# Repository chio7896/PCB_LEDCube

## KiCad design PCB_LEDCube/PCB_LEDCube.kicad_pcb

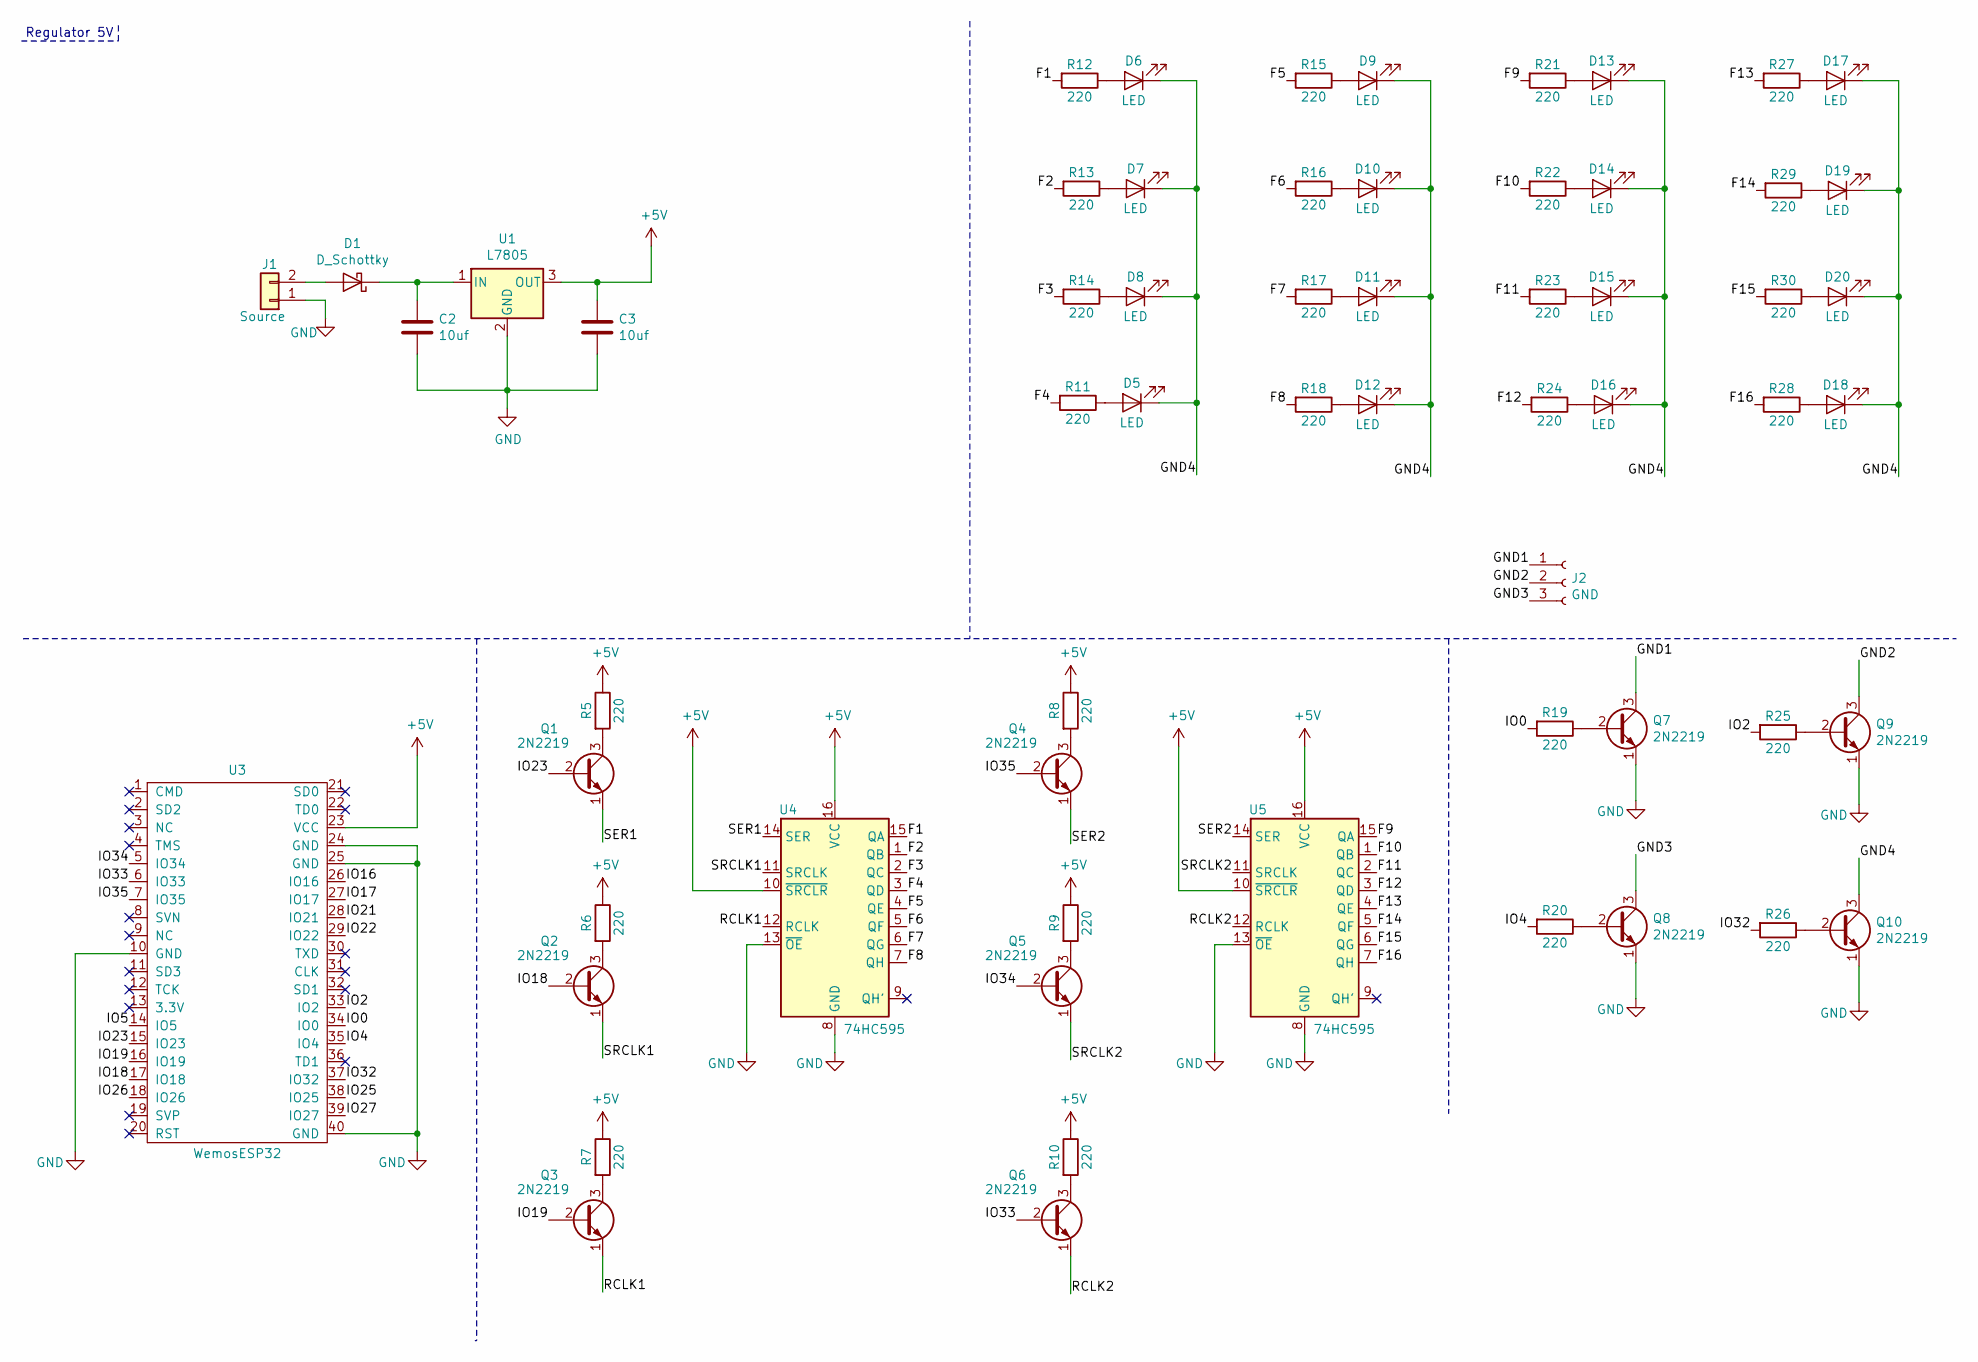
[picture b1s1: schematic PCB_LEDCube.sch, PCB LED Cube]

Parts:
C2, C3: 10uf; C_Disc_D5.0mm_W2.5mm_P5.00mm
D1: D_Schottky; D_A-405_P7.62mm_Horizontal
D5, D6, D7, D8, D9, D10, D11, D12, D13, D14, D15, D16, D17, D18, D19, D20: LED; LED_D5.0mm
J1: Source; TerminalBlock_bornier-2_P5.08mm
J2: GND; PinHeader_1x03_P2.54mm_Vertical
Q1, Q2, Q3, Q4, Q5, Q6, Q7, Q8, Q9, Q10: 2N2219; TO-92L_Inline
R5, R6, R7, R8, R9, R10, R11, R12, R13, R14, R15, R16, R17, R18, R19, R20, R21, R22, R23, R24, R25, R26, R27, R28, R29, R30: 220; R_Axial_DIN0207_L6.3mm_D2.5mm_P7.62mm_Horizontal
U1: L7805; TO-220-3_Vertical
U3: WemosESP32; Wemos_ESP32
U4, U5: 74HC595; DIP-16_W10.16mm_LongPads

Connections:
+5V: C3.1, R5.1, R6.1, R7.1, R8.1, R9.1, R10.1, U1.3 (OUT), U3.23 (VCC), U4.10 (~SRCLR), U4.16 (VCC), U5.10 (~SRCLR), U5.16 (VCC)
/F1: R12.2, U4.15 (QA)
/F2: R13.2, U4.1 (QB)
/F3: R14.2, U4.2 (QC)
/F4: R11.2, U4.3 (QD)
/F5: R15.2, U4.4 (QE)
/F6: R16.2, U4.5 (QF)
/F7: R17.2, U4.6 (QG)
/F8: R18.2, U4.7 (QH)
/F9: R21.2, U5.15 (QA)
/F10: R22.2, U5.1 (QB)
/F11: R23.2, U5.2 (QC)
/F12: R24.2, U5.3 (QD)
/F13: R27.2, U5.4 (QE)
/F14: R29.2, U5.5 (QF)
/F15: R30.2, U5.6 (QG)
/F16: R28.2, U5.7 (QH)
/GND1: J2.1, Q7.3 (C)
/GND2: J2.2, Q9.3 (C)
/GND3: J2.3, Q8.3 (C)
/GND4: D5.1 (K), D6.1 (K), D7.1 (K), D8.1 (K), D9.1 (K), D10.1 (K), D11.1 (K), D12.1 (K), D13.1 (K), D14.1 (K), D15.1 (K), D16.1 (K), D17.1 (K), D18.1 (K), D19.1 (K), D20.1 (K), Q10.3 (C)
/IO0: R19.2, U3.34 (IO0)
/IO2: R25.2, U3.33 (IO2)
/IO4: R20.2, U3.35 (IO4)
/IO5: U3.14 (IO5)
/IO16: U3.26 (IO16)
/IO17: U3.27 (IO17)
/IO18: Q2.2 (B), U3.17 (IO18)
/IO19: Q3.2 (B), U3.16 (IO19)
/IO21: U3.28 (IO21)
/IO22: U3.29 (IO22)
/IO23: Q1.2 (B), U3.15 (IO23)
/IO25: U3.38 (IO25)
/IO26: U3.18 (IO26)
/IO27: U3.39 (IO27)
/IO32: R26.2, U3.37 (IO32)
/IO33: Q6.2 (B), U3.6 (IO33)
/IO34: Q5.2 (B), U3.5 (IO34)
/IO35: Q4.2 (B), U3.7 (IO35)
/RCLK1: Q3.1 (E), U4.12 (RCLK)
/RCLK2: Q6.1 (E), U5.12 (RCLK)
/SER1: Q1.1 (E), U4.14 (SER)
/SER2: Q4.1 (E), U5.14 (SER)
/SRCLK1: Q2.1 (E), U4.11 (SRCLK)
/SRCLK2: Q5.1 (E), U5.11 (SRCLK)
GND: C2.2, C3.2, J1.1, Q7.1 (E), Q8.1 (E), Q9.1 (E), Q10.1 (E), U1.2 (GND), U3.10 (GND), U3.24 (GND), U3.25 (GND), U3.40 (GND), U4.8 (GND), U4.13 (~OE), U5.8 (GND), U5.13 (~OE)
unnamed: C2.1, D1.1 (K), U1.1 (IN)
unnamed: D1.2 (A), J1.2
unnamed: D5.2 (A), R11.1
unnamed: D6.2 (A), R12.1
unnamed: D7.2 (A), R13.1
unnamed: D8.2 (A), R14.1
unnamed: D9.2 (A), R15.1
unnamed: D10.2 (A), R16.1
unnamed: D11.2 (A), R17.1
unnamed: D12.2 (A), R18.1
unnamed: D13.2 (A), R21.1
unnamed: D14.2 (A), R22.1
unnamed: D15.2 (A), R23.1
unnamed: D16.2 (A), R24.1
unnamed: D17.2 (A), R27.1
unnamed: D18.2 (A), R28.1
unnamed: D19.2 (A), R29.1
unnamed: D20.2 (A), R30.1
unnamed: Q1.3 (C), R5.2
unnamed: Q2.3 (C), R6.2
unnamed: Q3.3 (C), R7.2
unnamed: Q4.3 (C), R8.2
unnamed: Q5.3 (C), R9.2
unnamed: Q6.3 (C), R10.2
unnamed: Q7.2 (B), R19.1
unnamed: Q8.2 (B), R20.1
unnamed: Q9.2 (B), R25.1
unnamed: Q10.2 (B), R26.1

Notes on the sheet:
Regulator 5V

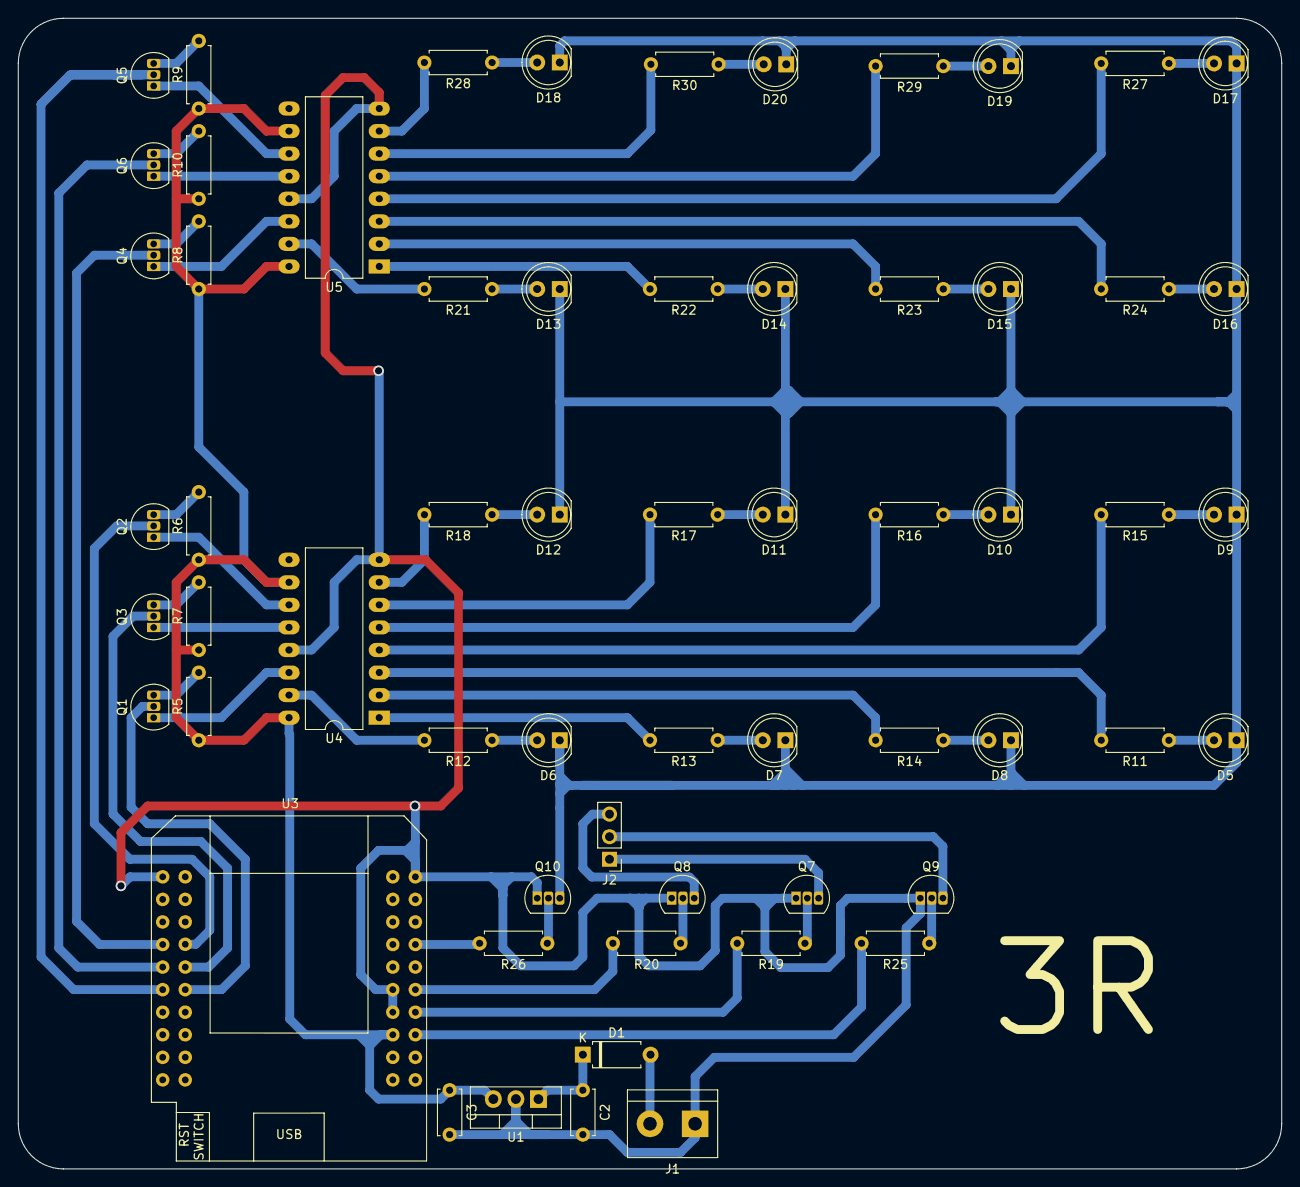
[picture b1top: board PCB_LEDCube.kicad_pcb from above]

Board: 2 copper layers, 142.2 x 129.5 mm, 61 parts (0 on the bottom side), 66 nets.

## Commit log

2020-04-11 add project
2020-04-12 add regulator
2020-04-12 Add footprints
2020-04-13 PCB TH hand
2020-04-13 pcb desing
